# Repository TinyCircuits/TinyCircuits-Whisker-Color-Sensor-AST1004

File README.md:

# TinyCircuits Wireling Color Sensor
# AST1004 Rev 2

The design files are located under design_files/ for the TinyCircuits AST1004 Rev 2 PCB. This is a Wireling board which measures the color and temperature of ambient or reflected light and also features a low power mode. Output resolution is 16-bit per each channel (Red, Green, and Blue). Includes bright white LEDs to aid sensing applications that can be toggled on or off.

Format is in Cadsoft Eagle format - Eagle version 6.2 was used for the original design.

For more infomation on this, check out the product page at TinyCircuits.com

# License:

Design by TinyCircuits.
All design files are released under the Creative Commons Attribution Share-Alike 3.0 License, see the following link for details: http://creativecommons.org/licenses/by-sa/3.0

All text above must be included in any redistribution or derived design

This project uses designs and concepts developed as part of the Arduino project and the LilyPad project.  The TinyCircuits design files themselves (schematics, PCB and libraries) are not directly derived from these works' design files and have been created new, however the concepts and basic architecture behind the TinyDuino and TinyLily products are derived and we thank the hard work of the organizations below for their contributions to open-source hardware:
  
Original Arduino Uno Design by Team Arduino

LilyPad Arduino Design by Leah Buechley and Sparkfun Electronics

Please support the open-source hardware community

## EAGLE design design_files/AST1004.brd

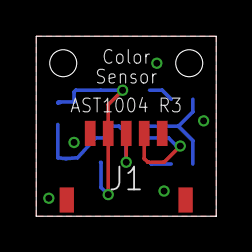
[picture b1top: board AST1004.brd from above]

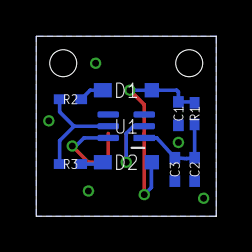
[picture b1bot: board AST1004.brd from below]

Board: 2 copper layers, 10.0 x 10.0 mm, 11 parts (9 on the bottom side), 8 nets.

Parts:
C1, C2: 1uF; C0402
C3: 0.1uF; C0402
D1, D2: QBLP674-IWM-NW; LED_TOP_2.8X1.4
J1: SM05B; JST_SH_5X1_EDGE
R1: 27.0; 0402
R2, R3: 5K; 0402
U1: TCS34725FN; TSL2572
U$1: DOCFIELD-TINYCIRCUITS-PCB

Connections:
GND: C1.2, C2.2, C3.2, J1.1, U1.3
unnamed: R2.1, R3.1, U1.5
unnamed: C2.1, C3.1, R1.2, U1.1
unnamed: D2.C, R3.2
unnamed: D1.C, R2.2
SCL: J1.3, U1.2
SDA: J1.4, U1.6
VCC: C1.1, D1.A, D2.A, J1.2, R1.1

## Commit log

2019-07-17 added images
2019-07-18 added image
2019-08-02 added datasheet
2019-09-24 fix program
2019-09-24 fix program, add LED toggle
2019-10-28 update program & name
2019-11-21 LED Datasheet
2019-12-17 updated documentation
2019-12-18 update program
2020-01-10 update images
2020-02-04 mass image update
2020-04-16 add some output
2020-08-14 Add CAD data
